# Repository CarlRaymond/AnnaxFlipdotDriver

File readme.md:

# Annax Flipdot Driver #

This is a driver for Annax flipdot display panels, with an Arduino nano or ESP8266 (Wemos D1 Mini) controller.

The controller consists of a row driver PC board, which contains the microcontroller,
and a column driver PC board. A span of panels can be any length. One row driver daisy
chains to all the panels, and each panel has its own column driver. The row and column
driver boards are connected together with a serial interface.

The row board acts as the master controller, and holds either an Arduino Nano or a WeMos D1 Mini
module.

The Nano has enough GPIO pins to supprt off-board connections to external controls,
supporting interactive applications. 

The WeMos D1 Mini is an ESP8266 device, with built-in WiFi capability. This allows using
the panel for signage, with remote configuration capability.

## Row Board ##
[Row board schematic](kicad/row_board/pdf/row_driver_schematic.pdf)

## Column Board ##
[Column board schematic](kicad/column_board/pdf/column_driver_schematic.pdf)

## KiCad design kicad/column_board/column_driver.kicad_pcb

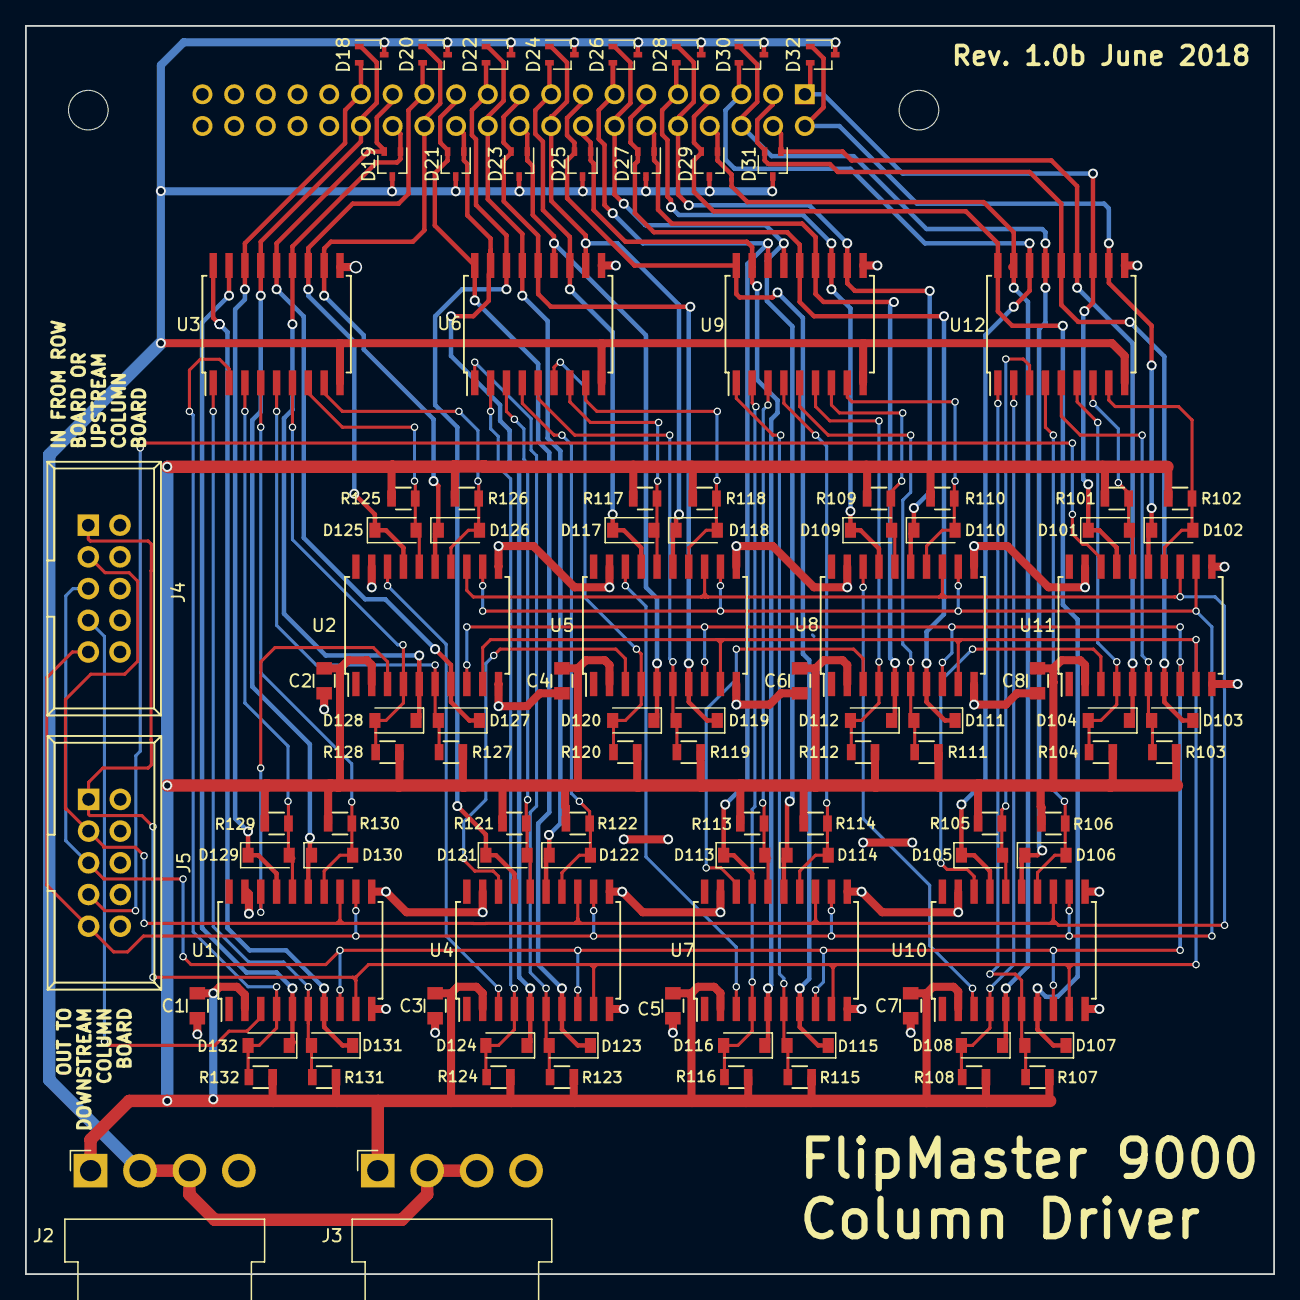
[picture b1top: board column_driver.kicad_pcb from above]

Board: 2 copper layers, 100.0 x 100.0 mm, 104 parts (1 on the bottom side), 80 nets.

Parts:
C1, C2, C3, C4, C5, C6, C7, C8: .1uF; C_0805
D18, D19, D20, D21, D22, D23, D24, D25, D26, D27, D28, D29, D30, D31, D32: BAV70W; SOT-323_SC-70
D101, D102, D103, D104, D105, D106, D107, D108, D109, D110, D111, D112, D113, D114, D115, D116, D117, D118, D119, D120, D121, D122, D123, D124, D125, D126, D127, D128, D129, D130, D131, D132: BAS16GW; D_SOD-123
J1: Panel column connector (female); Socket_Strip_Straight_2x20_Pitch2.54mm
J2: PWR_CHAIN_IN; JST_VH_B4PS-VH_1x04_P3.96mm_Horizontal
J3: PWR_CHAIN_OUT; JST_VH_B4PS-VH_1x04_P3.96mm_Horizontal
J4: DATA_CHAIN_IN; IDC_Header_Straight_10pins
J5: DATA_CHAIN_OUT; IDC_Header_Straight_10pins
R101, R102, R103, R104, R105, R106, R107, R108, R109, R110, R111, R112, R113, R114, R115, R116, R117, R118, R119, R120, R121, R122, R123, R124, R125, R126, R127, R128, R129, R130, R131, R132: 10K; R_0805
U1, U2, U4, U5, U7, U8, U10, U11: TPIC6B595; SOIC-20W_7.5x12.8mm_Pitch1.27mm
U3, U6, U9, U12: TBD62783; SOIC-18W_7.5x11.6mm_Pitch1.27mm

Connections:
+5V: C1.1, C2.1, C3.1, C4.1, C5.1, C6.1, C7.1, C8.1, J2.1, J3.1, R101.2, R102.2, R103.1, R104.2, R105.1, R106.1, R107.1, R108.1, R109.2, R110.2, R111.2, R112.2, R113.1, R114.1, R115.1, R116.1, R117.2, R118.2, R119.1, R120.2, R121.1, R122.1, R123.1, R124.1, R125.2, R126.2, R127.2, R128.2, R129.1, R130.1, R131.1, R132.1, U1.2, U2.2, U4.2, U5.2, U7.2, U8.2, U10.2, U11.2
+24V: D18.3, D19.3, D20.3, D21.3, D22.3, D23.3, D24.3, D25.3, D26.3, D27.3, D28.3, D29.3, D30.3, D31.3, D32.3, J2.2, J2.3, J3.2, J3.3, U3.9, U6.9, U9.9, U12.9
COL1: D32.2, D101.1, J1.1, U11.17, U12.12
COL2: D32.1, D102.1, J1.2, U11.15, U12.11
COL3: D31.2, D103.1, J1.3, U11.7, U12.14
COL4: D31.1, D104.1, J1.4, U11.5, U12.13
COL5: D30.2, D105.1, J1.5, U10.17, U12.16
COL6: D30.1, D106.1, J1.6, U10.15, U12.15
COL7: D29.2, D107.1, J1.7, U10.7, U12.18
COL8: D29.1, D108.1, J1.8, U10.5, U12.17
COL9: D28.2, D109.1, J1.9, U8.17, U9.12
COL10: D28.1, D110.1, J1.10, U8.15, U9.11
COL11: D27.2, D111.1, J1.11, U8.7, U9.14
COL12: D27.1, D112.1, J1.12, U8.5, U9.13
COL13: D26.2, D113.1, J1.13, U7.17, U9.16
COL14: D26.1, D114.1, J1.14, U7.15, U9.15
COL15: D25.2, D115.1, J1.15, U7.7, U9.18
COL16: D25.1, D116.1, J1.16, U7.5, U9.17
COL17: D24.2, D117.1, J1.17, U5.17, U6.12
COL18: D24.1, D118.1, J1.18, U5.15, U6.11
COL19: D23.2, D119.1, J1.19, U5.7, U6.14
COL20: D23.1, D120.1, J1.20, U5.5, U6.13
COL21: D22.2, D121.1, J1.21, U4.17, U6.16
COL22: D22.1, D122.1, J1.22, U4.15, U6.15
COL23: D21.2, D123.1, J1.23, U4.7, U6.18
COL24: D21.1, D124.1, J1.24, U4.5, U6.17
COL25: D20.2, D125.1, J1.25, U2.17, U3.12
COL26: D20.1, D126.1, J1.26, U2.15, U3.11
COL27: D19.2, D127.1, J1.27, U2.7, U3.14
COL28: D19.1, D128.1, J1.28, U2.5, U3.13
COL29: D18.2, D129.1, J1.29, U1.17, U3.16
COL30: D18.1, D130.1, J1.30, U1.15, U3.15
COL31: D131.1, U1.7, U3.18
COL32: D132.1, U1.5, U3.17
COL_REG_CLK: J4.9, J5.9, U1.12, U2.12, U4.12, U5.12, U7.12, U8.12, U10.12, U11.12
GND: C1.2, C2.2, C3.2, C4.2, C5.2, C6.2, C7.2, C8.2, J2.4, J3.4, J4.2, J4.4, J4.6, J4.8, J4.10, J5.2, J5.4, J5.6, J5.8, J5.10, U1.10, U1.11, U1.19, U2.10, U2.11, U2.19, U3.10, U4.10, U4.11, U4.19, U5.10, U5.11, U5.19, U6.10, U7.10, U7.11, U7.19, U8.10, U8.11, U8.19, U9.10, U10.10, U10.11, U10.19, U11.10, U11.11, U11.19, U12.10
unnamed: D101.2, R101.1, U11.16, U12.7
unnamed: D102.2, R102.1, U11.14, U12.8
unnamed: D103.2, R103.2, U11.6, U12.5
unnamed: D104.2, R104.1, U11.4, U12.6
unnamed: D105.2, R105.2, U10.16, U12.3
unnamed: D106.2, R106.2, U10.14, U12.4
unnamed: D107.2, R107.2, U10.6, U12.1
unnamed: D108.2, R108.2, U10.4, U12.2
unnamed: D109.2, R109.1, U8.16, U9.7
unnamed: D110.2, R110.1, U8.14, U9.8
unnamed: D111.2, R111.1, U8.6, U9.5
unnamed: D112.2, R112.1, U8.4, U9.6
unnamed: D113.2, R113.2, U7.16, U9.3
unnamed: D114.2, R114.2, U7.14, U9.4
unnamed: D115.2, R115.2, U7.6, U9.1
unnamed: D116.2, R116.2, U7.4, U9.2
unnamed: D117.2, R117.1, U5.16, U6.7
unnamed: D118.2, R118.1, U5.14, U6.8
unnamed: D119.2, R119.2, U5.6, U6.5
unnamed: D120.2, R120.1, U5.4, U6.6
unnamed: D121.2, R121.2, U4.16, U6.3
unnamed: D122.2, R122.2, U4.14, U6.4
unnamed: D123.2, R123.2, U4.6, U6.1
unnamed: D124.2, R124.2, U4.4, U6.2
unnamed: D125.2, R125.1, U2.16, U3.7
unnamed: D126.2, R126.1, U2.14, U3.8
unnamed: D127.2, R127.1, U2.6, U3.5
unnamed: D128.2, R128.1, U2.4, U3.6
unnamed: D129.2, R129.2, U1.16, U3.3
unnamed: D130.2, R130.2, U1.14, U3.4
unnamed: D131.2, R131.2, U1.6, U3.1
unnamed: D132.2, R132.2, U1.4, U3.2
unnamed: U1.18, U2.3
unnamed: U2.18, U4.3
unnamed: U4.18, U5.3
unnamed: U5.18, U7.3
unnamed: U7.18, U8.3
unnamed: U8.18, U10.3
unnamed: U10.18, U11.3
RC_DATA: J4.7, U1.3
RC_DATA_OUT: J5.7, U11.18
RC_SHIFT_CLK: J4.3, J5.3, U1.13, U2.13, U4.13, U5.13, U7.13, U8.13, U10.13, U11.13
~COL_EN: J4.1, J5.1, U1.9, U2.9, U4.9, U5.9, U7.9, U8.9, U10.9, U11.9
~RC_CLEAR: J4.5, J5.5, U1.8, U2.8, U4.8, U5.8, U7.8, U8.8, U10.8, U11.8

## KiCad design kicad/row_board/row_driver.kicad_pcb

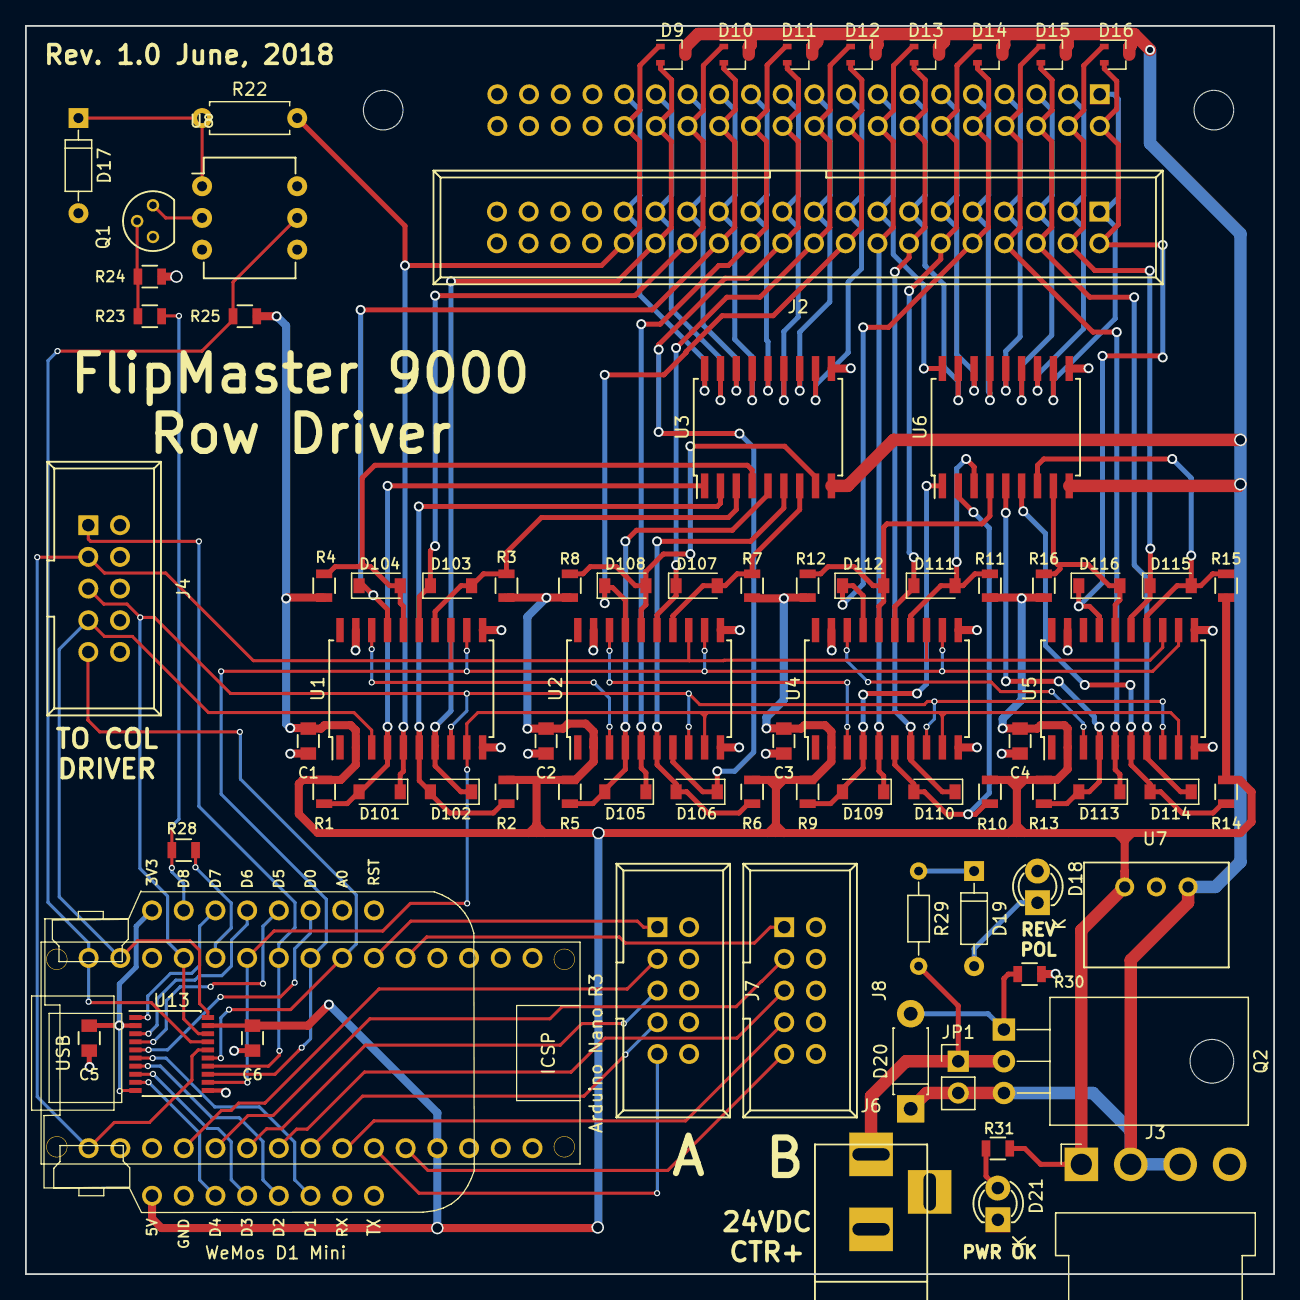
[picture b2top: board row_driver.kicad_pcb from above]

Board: 2 copper layers, 100.0 x 100.0 mm, 80 parts (1 on the bottom side), 91 nets.

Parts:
C1, C2, C3, C4, C5, C6: .1uF; C_0805
D9, D10, D11, D12, D13, D14, D15, D16: BAV70W; SOT-323_SC-70
D17, D19: 1N4148; D_DO-35_SOD27_P7.62mm_Horizontal
D18, D21: LED; LED-3MM
D20: 1N4742; D_DO-41_SOD81_P7.62mm_Horizontal
D101, D102, D103, D104, D105, D106, D107, D108, D109, D110, D111, D112, D113, D114, D115, D116: BAS16GW; D_SOD-123
J1: Panel row connector (female); Socket_Strip_Straight_2x20_Pitch2.54mm
J2: Row daisy chain connector (male); IDC_Header_Straight_40pins
J3: Conn_01x04; JST_VH_B4PS-VH_1x04_P3.96mm_Horizontal
J4: Column Board Connector; IDC_Header_Straight_10pins
J6: Barrel_Jack; BARREL_JACK
J7: Controller A; IDC_Header_Straight_10pins
J8: Controller B; IDC_Header_Straight_10pins
JP1: Jumper; Pin_Header_Straight_1x02_Pitch2.54mm
Q1: 2N3904; TO-92_Molded_Narrow
Q2: FQP47P06; TO-220_Horizontal
R1, R2, R3, R4, R5, R6, R7, R8, R9, R10, R11, R12, R13, R14, R15, R16, R25: 10K; R_0805
R22: 2K7; R_Axial_DIN0207_L6.3mm_D2.5mm_P7.62mm_Horizontal
R23: 1K; R_0805
R24: 2K2; R_0805
R28, R31: 470; R_0805
R29: 2K7; R_Axial_DIN0204_L3.6mm_D1.6mm_P7.62mm_Horizontal
R30: 2K7; R_0805
U1, U2, U4, U5: TPIC6B595; SOIC-20W_7.5x12.8mm_Pitch1.27mm
U3, U6: TBD62783; SOIC-18W_7.5x11.6mm_Pitch1.27mm
U7: WE-FDSM_DC/DC_5V; WPMDL9500xx
U8: 4N25; DIP-6_W7.62mm
U11: ArduinoNanoR3; Arduino_Nano_R3
U12: WeMos_mini; D1_mini_can_up
U13: TXB0108-PWR; SSOP-20_4.4x6.5mm_Pitch0.65mm

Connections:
+3V3: C5.1, U12.8, U13.2, U13.10
+5V: C1.1, C2.1, C3.1, C4.1, C6.2, J3.1, R1.1, R2.1, R3.1, R4.1, R5.2, R6.2, R7.2, R8.2, R9.1, R10.1, R11.1, R12.1, R13.2, R14.1, R15.2, R16.2, R25.1, R31.2, U1.2, U2.2, U4.2, U5.2, U7.3, U11.12, U12.9, U13.19
+24V: D9.3, D10.3, D11.3, D12.3, D13.3, D14.3, D15.3, D16.3, D20.1, J3.2, J3.3, JP1.2, Q2.3, U3.9, U6.9, U7.1
COL_REG_CLK: J4.9, U11.22, U13.15
COL_REG_CLK_3v3: U12.14, U13.6
CTRL_A0: J7.1, U11.21
CTRL_A1: J7.3, U11.4
CTRL_A2: J7.5, U11.6
CTRL_A3: J7.7, U11.8
CTRL_A4: J7.9, U11.10
CTRL_B0: J8.1, U11.20
CTRL_B1: J8.3, U11.5
CTRL_B2: J8.5, U11.7
CTRL_B3: J8.7, U11.9
CTRL_B4: J8.9, U11.11
GND: C1.2, C2.2, C3.2, C4.2, C5.2, C6.1, D17.2, D18.2, D21.1, J3.4, J4.2, J4.4, J4.6, J4.8, J4.10, J6.2, J7.2, J7.4, J7.6, J7.8, J7.10, J8.2, J8.4, J8.6, J8.8, J8.10, Q1.1, R24.2, R30.1, U1.10, U1.11, U1.19, U2.10, U2.11, U2.19, U3.10, U4.10, U4.11, U4.19, U5.10, U5.11, U5.19, U6.10, U7.2, U8.4, U11.14, U11.19, U12.10, U13.11
unnamed: D17.1, R22.1, U8.1
unnamed: D18.1, D19.2
unnamed: D19.1, R29.1
unnamed: D20.2, Q2.1, R30.2
unnamed: D21.2, R31.1
unnamed: D101.2, R1.2, U1.4, U3.1
unnamed: D102.2, R2.2, U1.6, U3.2
unnamed: D103.2, R3.2, U1.14, U3.3
unnamed: D104.2, R4.2, U1.16, U3.4
unnamed: D105.2, R5.1, U2.4, U3.5
unnamed: D106.2, R6.1, U2.6, U3.6
unnamed: D107.2, R7.1, U2.14, U3.7
unnamed: D108.2, R8.1, U2.16, U3.8
unnamed: D109.2, R9.2, U4.4, U6.1
unnamed: D110.2, R10.2, U4.6, U6.2
unnamed: D111.2, R11.2, U4.14, U6.3
unnamed: D112.2, R12.2, U4.16, U6.4
unnamed: D113.2, R13.1, U5.4, U6.5
unnamed: D114.2, R14.2, U5.6, U6.6
unnamed: D115.2, R15.1, U5.14, U6.7
unnamed: D116.2, R16.1, U5.16, U6.8
unnamed: J6.1, JP1.1, Q2.2, R29.2
unnamed: Q1.2, R23.1, R24.1
unnamed: Q1.3, U8.2
unnamed: U1.18, U2.3
unnamed: U2.18, U4.3
unnamed: U4.18, U5.3
RC_DATA: J4.7, U1.3, U11.29, U13.20
RC_DATA_3v3: U12.6, U13.1
RC_SHIFT_CLK: J4.3, U1.13, U2.13, U4.13, U5.13, U11.1, U13.16
RC_SHIFT_CLK_3v3: U12.3, U13.5
ROW1_H: J1.1, J2.1, U6.11
ROW1_L: D16.2, D116.1, J1.2, J2.2, U5.17
ROW2_H: J1.3, J2.3, U6.12
ROW2_L: D16.1, D115.1, J1.4, J2.4, U5.15
ROW3_H: J1.5, J2.5, U6.13
ROW3_L: D15.2, D114.1, J1.6, J2.6, U5.7
ROW4_H: J1.7, J2.7, U6.14
ROW4_L: D15.1, D113.1, J1.8, J2.8, U5.5
ROW5_H: J1.9, J2.9, U6.15
ROW5_L: D14.2, D112.1, J1.10, J2.10, U4.17
ROW6_H: J1.11, J2.11, U6.16
ROW6_L: D14.1, D111.1, J1.12, J2.12, U4.15
ROW7_H: J1.13, J2.13, U6.17
ROW7_L: D13.2, D110.1, J1.14, J2.14, U4.7
ROW8_H: J1.15, J2.15, U6.18
ROW8_L: D13.1, D109.1, J1.16, J2.16, U4.5
ROW9_H: J1.17, J2.17, U3.11
ROW9_L: D12.2, D108.1, J1.18, J2.18, U2.17
ROW10_H: J1.19, J2.19, U3.12
ROW10_L: D12.1, D107.1, J1.20, J2.20, U2.15
ROW11_H: J1.21, J2.21, U3.13
ROW11_L: D11.2, D106.1, J1.22, J2.22, U2.7
ROW12_H: J1.23, J2.23, U3.14
ROW12_L: D11.1, D105.1, J1.24, J2.24, U2.5
ROW13_H: J1.25, J2.25, U3.15
ROW13_L: D10.2, D104.1, J1.26, J2.26, U1.17
ROW14_H: J1.27, J2.27, U3.16
ROW14_L: D10.1, D103.1, J1.28, J2.28, U1.15
ROW15_H: J1.29, J2.29, U3.17
ROW15_L: D9.2, D102.1, J1.30, J2.30, U1.7
ROW16_H: J1.31, J2.31, U3.18
ROW16_L: D9.1, D101.1, J1.32, J2.32, R22.2, U1.5
ROW_REG_CLK: U1.12, U2.12, U4.12, U5.12, U11.23, U13.13
ROW_REG_CLK_3v3: U12.12, U13.8
SENSE_EN: R28.2, U11.26
SENSE_EN_3v3: R23.2, R28.1, U12.7
~COL_EN: J4.1, U11.24, U13.14
~COL_EN_3v3: U12.13, U13.7
~RC_CLEAR: J4.5, U1.8, U2.8, U4.8, U5.8, U11.27, U13.18
~RC_CLR_3v3: U12.5, U13.3
~ROW_EN: U1.9, U2.9, U4.9, U5.9, U11.25, U13.12
~ROW_EN_3v3: U12.11, U13.9
~SENSE: R25.2, U8.5, U11.30, U13.17
~SENSE_3v3: U12.4, U13.4

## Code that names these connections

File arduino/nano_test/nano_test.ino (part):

#include <SPI.h>
#include <avr/wdt.h>

#define COL_REG_CLK 4
#define ROW_REG_CLK 5
#define COL_EN 6
#define ROW_EN 7
#define SENSE_EN 8
#define RC_CLEAR 9
#define RC_DATA 11
#define RC_SHIFT_CLK 13
#define SENSE 12

#define CTRL_A0 3
#define CTRL_A1 14
#define CTRL_A2 16
#define CTRL_A3 18
//#define CTRL_A4
#define CTRL_B0 2
#define CTRL_B1 15
#define CTRL_B2 17
#define CTRL_B3 19
//#define CTRL_B4

SPISettings SPImode = SPISettings(1000000, LSBFIRST, SPI_MODE0);

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
void setup() {

  pinMode(COL_REG_CLK, OUTPUT);
  pinMode(ROW_REG_CLK, OUTPUT);
  pinMode(COL_EN, OUTPUT);
  pinMode(ROW_EN, OUTPUT);
  pinMode(RC_CLEAR, OUTPUT);
  pinMode(RC_DATA, OUTPUT);
  pinMode(RC_SHIFT_CLK, OUTPUT);
  pinMode(SENSE_EN, OUTPUT);

  pinMode(CTRL_A0, INPUT);
  pinMode(CTRL_A1, INPUT);
  pinMode(CTRL_A2, INPUT);
  pinMode(CTRL_A3, INPUT);
  pinMode(CTRL_B0, INPUT);
  pinMode(CTRL_B1, INPUT);
  pinMode(CTRL_B2, INPUT);
  pinMode(CTRL_B3, INPUT);
  pinMode(SENSE, INPUT);

  digitalWrite(SENSE_EN, LOW);
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
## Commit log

2018-05-16 Pass DRC on row driver schematic
2018-05-16 Add footprints
2018-05-17 More footprint selection
2018-05-18 Cleanup; add test points; add column line pullup/pulldowns
2018-05-19 Row board nearly done; added test points
2018-05-20 Add column board
2018-05-21 Finish column board schematic
2018-05-21 Starting row board layout
2018-05-21 Replace BAV23 with BAS16GW
2018-05-26 Begin layout
2018-05-30 Add reverse power protection; data sheets
2018-06-01 Prior to deleting ESP8266
2018-06-08 Combine two controllers
2018-06-10 Routed shift registers and row connectors
2018-06-11 Routed all but controllers
2018-06-15 Finished routing row board; cleaning up.
2018-06-15 Fully routed row board
2018-06-22 Mostly routed column board
2018-06-22 Nearly done routing column board.
2018-06-22 All connections routed. Board still ugly.
2018-06-23 Parts positioned
2018-06-24 About to move high side drivers
2018-06-25 Final routing
2018-06-26 Fully routed column board
2018-06-26 Cleanup on column board
2018-06-26 Update column board
2018-06-27 Add Gerber and DXF files for row and column boards
2018-07-01 Add project-local footprints and 3D models
2018-07-01 Localize footprints and 3D models in column board; add images
2018-07-01 Remove row_driver-rescue library from row driver schematic
2018-07-01 Moved images; added to readme.md
2018-07-14 Add Nano test program
2018-07-18 Set parameters for single-panel mode
2018-07-18 Clean up flipColOn and flipColOff
2018-07-19 Flesh out column and gap sense
2018-07-23 Add setColumn()
2018-07-25 Preliminary snake game
2018-07-27 Pretty snaky.
2018-07-28 Fix setColumn
2018-07-28 Add WeMos test
2018-08-01 Two-player mode
2018-08-06 Add snake reversal feature
2018-08-27 Created FlipdotPanel library to abstract away the controller.
2018-08-27 Add better setColumn and setAllColumns.
2018-08-28 Update snake.ino to use FlipdotPanel library.
2018-09-08 Update Snake to use FlipdotPanel library.
